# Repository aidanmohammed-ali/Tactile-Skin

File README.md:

# Tactile-Skin

This project focuses on creating a thin, flexible tactile skin that measures mechanical pressure, rather than just proximity. This repository contains the firmware and signal processing logic to convert physical deformation and capacitance into usable digital data and the schematics and Gerber files for the requisite hardware.

## Repository Structure

### Firmware
The core software running on the microcontroller, built using PlatformIO. It handles high-speed analog acquisition from the skin matrix and packs it for serial transmission.
* `/src`: Main firmware source files (`.c` & `.cpp`).
* `/include`: Global header files (`.h`).
* `platformio.ini`: The core PlatformIO configuration script.

### Tools (`/tools`)
* `/common`: Shared, hardware-agnostic C++ data engine containing the core signal processing logic and GUI rendering requirements. Folder required to compile both visualiser and raw-streaming.
* `/visualiser`: A high-performance, cross-platform desktop utility built with Raylib. Features include:
  * **Multi-Instance Isolation:** Run multiple parallel instances side-by-side to monitor independent microcontrollers simultaneously.
  * **Dynamic Port Mapping:** Hot-swap hardware link contexts on-the-fly via an integrated UI selector.
  * **Zero-Lag Simulation Mode:** Automated fallback to a high-fidelity Gaussian simulation model when running offline.
  * **Dynamic Profile Loading:** Real-time parameter loading via local `.ini` configuration files to calibrate individual sensor variations dynamically without recompiling the codebase.
* `/raw-streaming`: A utility based on the visualiser for streaming the raw sensor data without any signal processing. Raw data across a specified time frame can be saved in `.csv` format and used for data analysis.

### Hardware (`/hardware`)
* `/fpc`: Flexible Printed Circuit manufacturing files.
  * Complete production-ready Gerber packages.
* `/pcb`: Main rigid Printed Circuit Board design histories.
  * Main interface between the sensor and microcontroller.

## Sensor Hardware

The tactile skin is built around a 16 x 8 capacitive matrix sensor. Each taxel in the matrix responds to local pressure-induced deformation, producing a change in capacitance that can be mapped into a two-dimensional tactile image. This layout provides a compact sensing surface while preserving enough spatial resolution to estimate where and how an object contacts the skin.

The signal collection board interfaces the sensor matrix with AD7142 capacitance-to-digital converters and an STM32F411CEU6 microcontroller. The AD7142 devices convert small capacitance changes from the tactile array into digital measurements, while the STM32 firmware coordinates sensor scanning, data acquisition, packet formatting, and USB serial transmission to the host computer. Together, the flexible sensor and collection board form a complete tactile feedback module for robotic manipulation experiments.

## Tactile Sensor Application Demo

This demo shows a robot using tactile feedback to grasp and place a block more accurately. When the robot picks up the block, the tactile contact pattern is visualised on the computer as a red region on the green heat map. The robot uses this tactile pattern to estimate an offset for the final placement position, allowing it to compensate when the YOLO vision prediction is inaccurate or when the block is disturbed after detection.

In the first trial, the robot detects the block with computer vision, picks it up, and places it in the holder. In the second trial, the block is manually moved after YOLO detection, but the robot still places it successfully because the tactile feedback corrects the placement position during the task.

## Contribution Guidelines

To keep the project history clean and professional, please follow these conventions:

### Git Commit Prefixes
Use **Conventional Commits**. Start every commit message with one of these:
* **`Docs:`** Documentation changes or code comments (e.g., `Docs: update README`).
* **`Feat:`** New features or logic (e.g., `Feat: implementation of scan loop`).
* **`Fix:`** Bug fixes (e.g., `Fix: corrected index overflow`).
* **`Chore:`** Maintenance tasks, library imports, or project scaffolding (e.g., `Chore: import USB core libraries`).

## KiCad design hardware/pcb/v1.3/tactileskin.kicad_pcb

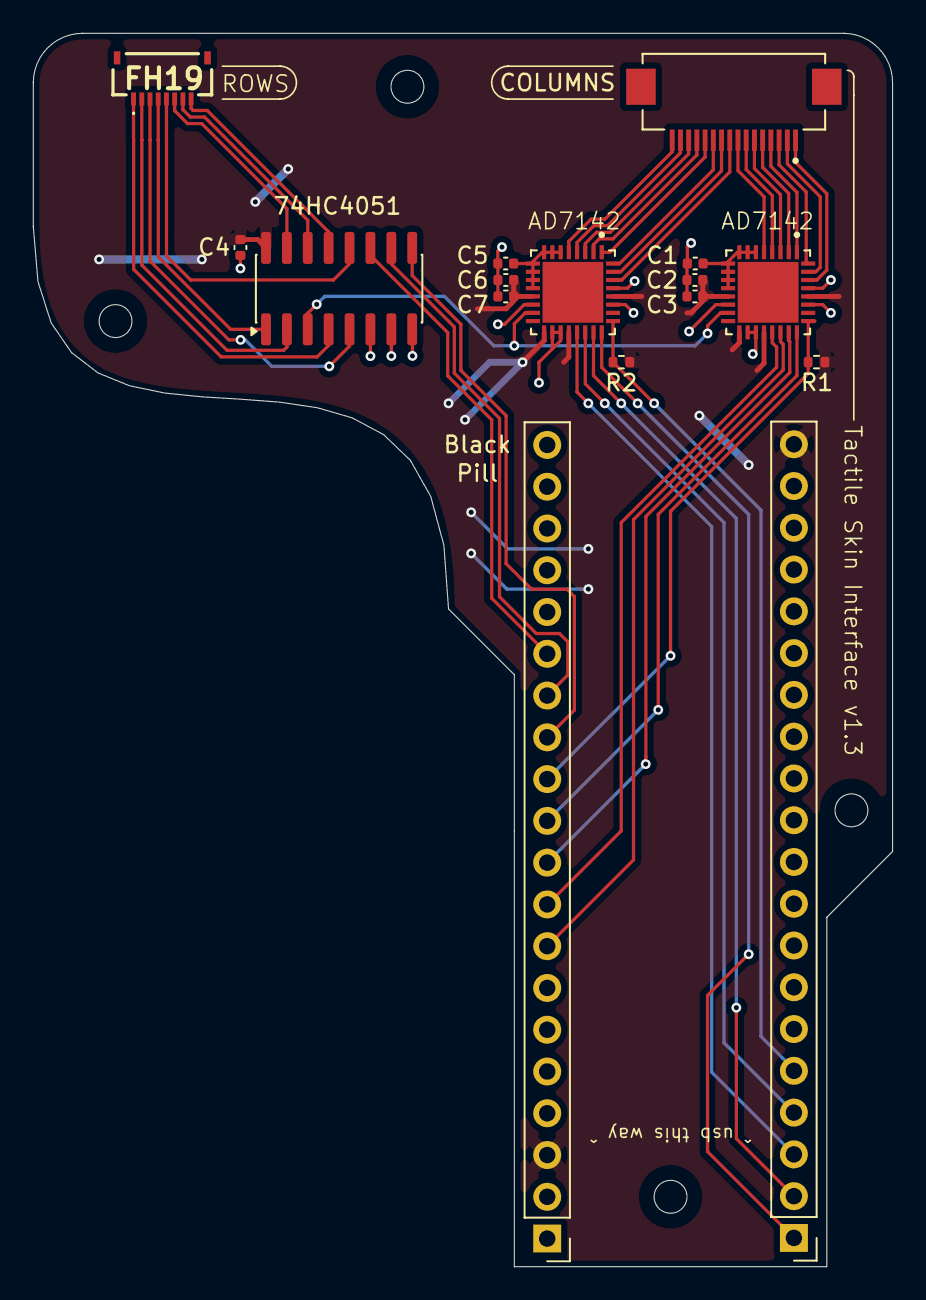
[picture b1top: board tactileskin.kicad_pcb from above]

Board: 2 copper layers, 52.3 x 75.0 mm, 16 parts (0 on the bottom side), 43 nets.

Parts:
74HC4051: 74HC4051; SOIC-16_3.9x9.9mm_P1.27mm
AD7142_a1, AD7142_b1: QFN50P500X500X100-33N
Black: Conn_01x20_Pin; PinHeader_1x20_P2.54mm_Vertical
C1, C5: 10n; C_0402_1005Metric
C2, C6: 0.1u; C_0402_1005Metric
C3, C7: 10u; C_0402_1005Metric
C4: 100n; C_0402_1005Metric
COLUMNS: FH12-16S-0.5SH_55_; HIROSE_FH12-16S-0.5SH_55_
FH19: FH19C-8S-0.5SH_10_; FH19C8S05SH10
J_MCU_LEFT1: Conn_01x20_Pin; PinHeader_1x20_P2.54mm_Vertical
R1, R2: 2.2k; R_0402_1005Metric

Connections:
+3.3V: 74HC4051.16 (VCC), AD7142_a1.13 (AVCC), AD7142_a1.17 (DVCC), AD7142_a1.20 (VDRIVE), AD7142_a1.28 (Vref+), AD7142_b1.13 (AVCC), AD7142_b1.17 (DVCC), AD7142_b1.20 (VDRIVE), AD7142_b1.28 (Vref+), Black.3, C2.1, C3.1, C4.1, C6.1, C7.1, J_MCU_LEFT1.20, R1.1, R2.1
+5V: Black.1, J_MCU_LEFT1.18
/A0: 74HC4051.11 (S0), Black.15
/A1: 74HC4051.10 (S1), Black.14
/A2: 74HC4051.9 (S2), Black.13
/A3: AD7142_a1.25 (~INT), Black.12, R1.2
/A4: AD7142_a1.24 (~CS), Black.11
/A5: AD7142_a1.23 (SCLK), Black.10
/A6: AD7142_a1.21 (SDO), Black.9
/A7: AD7142_a1.22 (SDI), Black.8
/A8: AD7142_b1.25 (~INT), J_MCU_LEFT1.5, R2.2
/B12: AD7142_b1.24 (~CS), J_MCU_LEFT1.1
/B13: AD7142_b1.23 (SCLK), J_MCU_LEFT1.2
/B14: AD7142_b1.21 (SDO), J_MCU_LEFT1.3
/B15: AD7142_b1.22 (SDI), J_MCU_LEFT1.4
GND: 74HC4051.6 (~E), 74HC4051.7 (VEE), 74HC4051.8 (GND), AD7142_a1.14 (AGND), AD7142_a1.18 (DGND1), AD7142_a1.19 (DGND2), AD7142_a1.27 (TEST), AD7142_a1.29 (Vref-), AD7142_b1.14 (AGND), AD7142_b1.18 (DGND1), AD7142_b1.19 (DGND2), AD7142_b1.27 (TEST), AD7142_b1.29 (Vref-), Black.2, C1.2, C2.2, C3.2, C4.2, C5.2, C6.2, C7.2, J_MCU_LEFT1.19
unnamed: AD7142_a1.30 (CIN0), COLUMNS.1
unnamed: AD7142_a1.31 (CIN1), COLUMNS.2
unnamed: AD7142_a1.32 (CIN2), COLUMNS.3
unnamed: AD7142_a1.1 (CIN3), COLUMNS.4
unnamed: AD7142_a1.2 (CIN4), COLUMNS.5
unnamed: AD7142_a1.3 (CIN5), COLUMNS.6
unnamed: AD7142_a1.4 (CIN6), COLUMNS.7
unnamed: AD7142_a1.5 (CIN7), COLUMNS.8
unnamed: AD7142_a1.6 (CIN8), AD7142_a1.7 (CIN9), AD7142_a1.8 (CIN10), AD7142_a1.9 (CIN11), AD7142_a1.10 (CIN12), AD7142_a1.11 (CIN13), AD7142_a1.12 (CSHIELD), C1.1
unnamed: 74HC4051.3 (A), AD7142_a1.15 (SRC), AD7142_b1.15 (SRC)
unnamed: AD7142_b1.30 (CIN0), COLUMNS.9
unnamed: AD7142_b1.31 (CIN1), COLUMNS.10
unnamed: AD7142_b1.32 (CIN2), COLUMNS.11
unnamed: AD7142_b1.1 (CIN3), COLUMNS.12
unnamed: AD7142_b1.2 (CIN4), COLUMNS.13
unnamed: AD7142_b1.3 (CIN5), COLUMNS.14
unnamed: AD7142_b1.4 (CIN6), COLUMNS.15
unnamed: AD7142_b1.5 (CIN7), COLUMNS.16
unnamed: AD7142_b1.6 (CIN8), AD7142_b1.7 (CIN9), AD7142_b1.8 (CIN10), AD7142_b1.9 (CIN11), AD7142_b1.10 (CIN12), AD7142_b1.11 (CIN13), AD7142_b1.12 (CSHIELD), C5.1
unnamed: 74HC4051.13 (A0), FH19.8
unnamed: 74HC4051.14 (A1), FH19.7
unnamed: 74HC4051.15 (A2), FH19.6
unnamed: 74HC4051.12 (A3), FH19.5
unnamed: 74HC4051.1 (A4), FH19.4
unnamed: 74HC4051.5 (A5), FH19.3
unnamed: 74HC4051.2 (A6), FH19.2
unnamed: 74HC4051.4 (A7), FH19.1

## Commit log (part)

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2026-04-29 Docs: initialise project structure and technical overview
2026-04-29 Docs: implementation of scanning skeleton and directory structure
2026-04-29 Docs: addition of contribution guidelines
2026-04-29 Feat: addition of core scanning library and bridge functions
2026-04-29 Fix: typo in main.cpp
2026-04-30 Feat: implementation of grid scanning logic and hardware abstraction
2026-05-01 Feat: implementation of settling time delay
2026-05-01 Feat: addition of signal processing with baseline calibration and noise thresholding
2026-05-01 Docs: typo in REAME
2026-05-01 Feat: implementation of hardware bridge and processing loop
2026-05-05 Feat: addition of PlatformIO and ESP-IDF CMake build configuration
2026-05-05 Docs: updates to README with new repository structure
2026-05-05 Fix: refactoring matrix_scan logic and fix pointer initialisation bug
2026-05-05 Feat: implementation of native ESP-IDF app_main loop
2026-05-05 Feat: migration of tactile processing to main
2026-05-13 Interface PCB v1
2026-05-13 Restore .gitignore
2026-05-14 Merge pull request #2 from ummo-n/pcb
    Feat: addition of Interface PCB v1
2026-05-14 Feat: addition of baud rate setting to PlatformIO
2026-05-14 Docs: removal of unnecessary CMake files
2026-05-14 Feat: addition of quadratic calibration using Cramer's rule for tactile processing
2026-05-14 Feat: implementation of analog read logic
2026-05-14 Fix: corrected logic within tactile processing to remove redundant function arguments
2026-05-14 Fix: renamed get_sensor_value to read_analog for generic hardware support
2026-05-14 Feat: additions to matrix scanning library for parallel scanning
2026-05-14 Feat: migration to STM32 and PlatformIO
2026-05-17 Fix: adjusted fpc connector spacing and minor routing errors
2026-05-17 Docs: clearer labeling v1.0 and v1.1
2026-05-17 Docs: updates to documentation for tactile processing library
2026-05-17 Docs: updates to the documentation for matrix scan library
2026-05-17 Feat: add FPC and Gerber folder with EasyEDA designed Gerber Files for FPC and adapters
2026-05-18 Fix: corrected pointer error in tactile processing
2026-05-18 Fix: corrected data type for tactile processing curve fit function
2026-05-18 Fix: changed devboard orientation
2026-05-18 Feat: migration to STM32 for main loop and integration of processing pipeline
2026-05-20 Feat: implementation of AD7142 initialisation
2026-05-20 Feat: implementation of calibration handling and interrupt handling
2026-05-21 Docs: migration of matrix_scan library to standard project structure
2026-05-21 Docs: migration of tactile_proc library to standard project structure
2026-05-21 Docs: reallocation of hardware abstraction configuration to include directory
2026-05-21 Docs: reallocation of main logic to src directory
2026-05-21 Docs: updated platformio.ini to use default framework layout
2026-05-21 Docs: removal of redundant version tags and customisation added to HAL configuration header file
2026-05-22 Docs: updated documentation for return values in matrix_scan library
2026-05-22 Docs: updated documentation in main MCU logic
2026-05-22 Chore: import STMicroelectronics USB core and CDC class middleware libraries
2026-05-22 Feat: implementation of native USB CDC configuration
2026-05-22 Docs: updated README.md
2026-05-23 Feat: integration of native USB data transmission into core processing loop
2026-05-23 Fix: resolved USB CDC middleware and low-level link layer bindings
2026-05-24 Feat: implementation of cross-platform serial engine and matrix rendering pipeline
2026-05-24 Docs: integrates local gitignore rule configurations for build safety
2026-05-24 Feat: transition to smooth thermal mapping engine and Gaussian simulation fallback
2026-05-24 Docs: updated gitignore for local development Makefile
2026-05-25 Feat: implementation of multi-point hardware calibration wizard
2026-05-27 Feat: Added mounting holes and a different 8-pin connector
2026-05-27 Merge pull request #9 from ummo-n/pcb-versions
    Feat: added mounting holes and a different 8-pin connector
2026-05-27 Feat: addition of support for dual-CDC interrupts
2026-05-28 Chore: import of raygui library
2026-05-28 Feat: implementation of COM Port selection logic
2026-05-29 Feat: addition of further COM Ports for each operating system
2026-05-29 Fix: resolved compiler errors and COM Port selection errors for Windows
2026-05-29 Fix: resolved stuttering on Linux
2026-05-31 Chore: reorganised directory structure
2026-05-31 Docs: update README.md
2026-05-31 Docs: addition of README.md for visualiser
2026-06-02 Docs: update README.md for visualiser
2026-06-03 Added ROS2 code used for application part
2026-06-03 Fix: corrected matrix scan hardware timing and MUX addressing
2026-06-03 Fix: adjusted processing parameters to resolve signal saturation
2026-06-03 Fix: correction of SPI logic, interrupt handling and hardware timing
2026-06-03 Feat: addition of visual scaling
2026-06-03 Fix: removal of troubleshooting artifact
2026-06-05 Feat: updated timing logic for scanning library
2026-06-05 Fix: corrections to the SPI communication logic and pin assignments
2026-06-05 Feat: implementation of PC-side signal processing logic into visualiser code
2026-06-05 Feat: addition of PC-side signal processing logic
2026-06-05 Docs: updated comment for legacy code in visualiser
2026-06-05 Feat: implementation of 5-sample median filtering and 2D spatial smoothing
2026-06-06 Docs: updated README.md for visualiser
2026-06-06 Chore: rearranged tools directory
2026-06-06 Chore: rearranged tools directory for raygui.h
2026-06-07 Feat: updated color scheme for better readability
2026-06-09 Fix: addition of delay for scanning logic
2026-06-09 Fix: correction to operations order for parallel scan
2026-06-09 Feat: implementation of magic word for USB CDC
2026-06-09 Chore: tuning values for filtering
2026-06-10 Feat: implementation of interrupt logic
2026-06-10 Chore: cleaned up visualiser code
2026-06-10 Feat: addition of continuity into scanning logic
2026-06-10 Chore: tuning offset values
2026-06-10 Feat: additional signal processing to reduce noise and random fluctuation
2026-06-10 Feat: addition of unsharp masking for signal processing
2026-06-12 Feat: addition of variable processing configurations into the main processing logic
2026-06-12 Feat: implementation of configuration selection within visualiser
2026-06-12 Feat: addition of configuration loading logic and header file
2026-06-12 Feat: addition of default config.ini file
2026-06-13 Feat: addition of trimming moving average filter for signal processing
2026-06-13 Chore: adjustments to the AFE Offset for both CDC chips
2026-06-13 Feat: addition of .ini configuration files for sensor1 and sensor2
2026-06-14 Fix: corrected size error for GuiComboBox
2026-06-15 Fix: corrected variable name in visualiser main.cpp
2026-06-26 ROS2 Humble Application Code
2026-06-28 Docs: generalise ROS2 workspace paths
2026-06-29 Feat: addition of raw-streaming tool for raw data analysis
2026-06-29 Docs: update README.md for raw-streaming
2026-06-30 Chore: addition of the saved raw data to .gitignore
2026-06-30 Feat: addition of data saving to a .csv file
